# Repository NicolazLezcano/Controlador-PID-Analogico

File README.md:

# Controlador PID Analógico: Diseño, Simulación e Implementación

Este repositorio contiene el desarrollo integral de un controlador PID analógico, desde el modelado teórico y la simulación hasta el diseño de PCB y la validación en hardware real.
---

---

## 📋 Características Técnicas
* **Topología:** Controlador PID Analógico.
* **Software de Diseño:** KiCad (v9.0.7).
* **Simulación:** LTspice (v26.0.1).
* **Diseño de PCB:** Single-layer con plano de masa (GND).
* **Documentación:** Informe técnico completo incluido en la carpeta `/docs`.

---

## 📈 Simulación en LTspice
Antes del diseño físico, se validó la respuesta temporal del controlador utilizando **LTspice**. El objetivo fue ajustar las constantes para minimizar el *overshoot* y optimizar el tiempo de establecimiento ($t_s$).

$$u(t) = K_p e(t) + K_i \int_{0}^{t} e(\tau) d\tau + K_d \frac{de(t)}{dt}$$

| Controlador PID | Respuesta al Escalón |
| :---: | :---: |
|  |  |

> **Nota:** Los archivos de simulación (`.asc`) están disponibles en la carpeta `/simulation` para su replicación.

---

## 🎨 Diseño de Hardware (KiCad)
El diseño del PCB se optimizó para facilitar el prototipado rápido y garantizar la integridad de la señal frente a ruidos e interferencias.

### Esquemático (Hoja Raíz)
Se utilizó un diseño jerárquico para separar las etapas de adquisición, procesamiento de error y potencia.

| Sensor | PID |
| :---: | :---: |
|  |  |

| PPM | Potencia |
| :---: | :---: |
|  |  |

### Layout y Ruteado
* **Integridad de Señal:** Se implementó un plano de masa (**Copper Pour**) para reducir la impedancia de retorno.
* **Single-Layer:** El ruteado se realizó exclusivamente en la capa inferior (**Back Copper**) para simplificar la manufactura manual.

| Ruteado de Pistas (Sin relleno) | Diseño Final (Con Plano de Masa) |
| :---: | :---: |
|  |  |

| Modelo 3D (Vista Frontal) | Modelo 3D (Vista Posterior) |
| :---: | :---: |
|  |  |

---

## 🛠️ Implementación y Resultados Reales
El proyecto concluyó con la fabricación física y la integración con el sensor y la carga, comparando los resultados experimentales con los simulados.

### Montaje y Calidad de Soldadura
| Vista Frontal (Componentes) | Vista Posterior (Soldadura) |
| :---: | :---: |
|  |  |

### Integración del Sistema
Se validó el lazo cerrado conectando el controlador a la carga (planta térmica) y al sensor de temperatura LM35DZ, verificando la estabilidad del sistema ante perturbaciones.

---

## 📂 Estructura del Repositorio
* `/kicad`: Archivos fuente del proyecto (`.kicad_pro`, `.kicad_sch`, `.kicad_pcb`).
* `/simulation`: Archivos de LTspice y capturas de ondas.
* `/img`: Imágenes, renders y capturas utilizadas en este README.
* `/docs`: Informe técnico detallado y lista de materiales (BOM).
* `/manufacturing`: Documentación de manufactura dividida en capas (`gerbers/`) y perforaciones (`drill/`). Incluye un archivo .zip listo para servicios de prototipado rápido.

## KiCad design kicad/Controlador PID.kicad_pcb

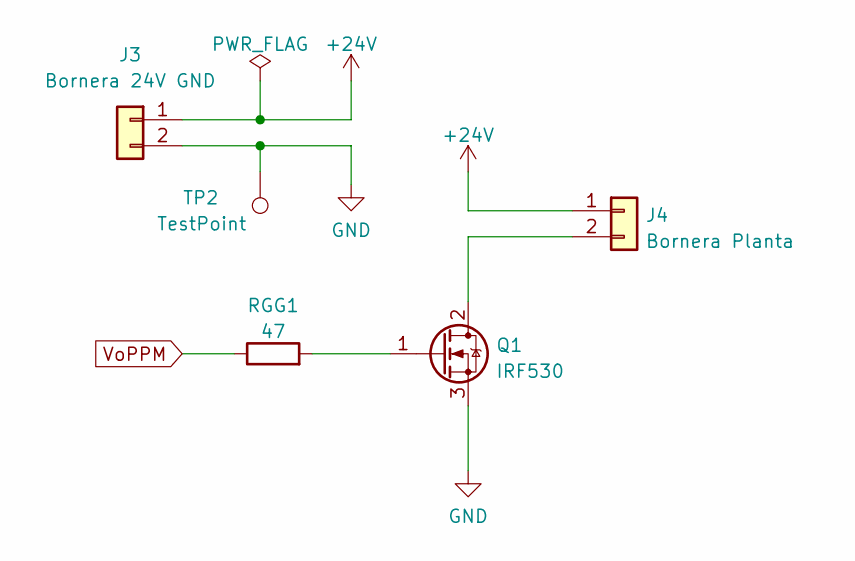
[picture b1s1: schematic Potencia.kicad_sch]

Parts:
J3: Bornera 24V GND; TerminalBlock_bornier-2_P5.08mm
J4: Bornera Planta; TerminalBlock_bornier-2_P5.08mm
Q1: IRF530; TO-220-3_Vertical Nico
RGG1: 47; R_Axial_DIN0207_L6.3mm_D2.5mm_P10.16mm_Horizontal Nico
TP2: TestPoint; PinHeader_1x01_P2.54mm_Vertical Nico

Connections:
+24V: J3.1, J4.1
GND: J3.2, Q1.3 (S), TP2.1; also elsewhere on the board
unnamed: J4.2, Q1.2 (D)
unnamed: Q1.1 (G), RGG1.2
VoPPM: RGG1.1; also elsewhere on the board

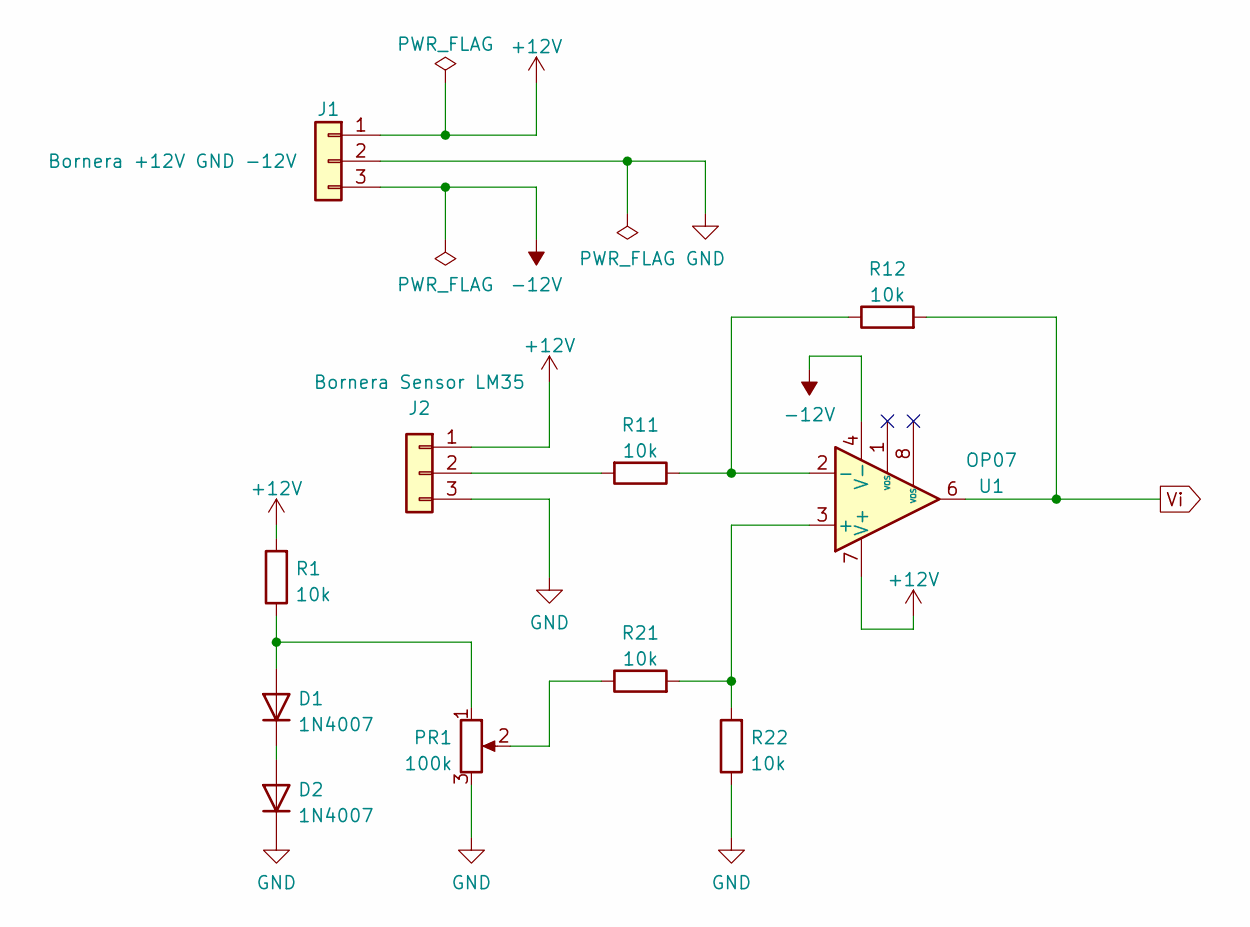
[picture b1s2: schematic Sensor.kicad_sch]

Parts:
D1, D2: 1N4007; D_DO-41_SOD81_P10.16mm_Horizontal
J1: Bornera +12V GND -12V; TerminalBlock_bornier-3_P5.08mm
J2: Bornera Sensor LM35; TerminalBlock_bornier-3_P5.08mm
PR1: 100k; Potentiometer_Piher_PC-16_Single_Horizontal
R1, R11, R12, R21, R22: 10k; R_Axial_DIN0207_L6.3mm_D2.5mm_P10.16mm_Horizontal Nico
U1: OP07; DIP-8_W7.62mm_LongPads Nico

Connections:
+12V: J1.1, J2.1, R1.2, U1.7 (V+); also elsewhere on the board
-12V: J1.3, U1.4 (V-); also elsewhere on the board
GND: D2.1 (K), J1.2, J2.3, PR1.3, R22.1; also elsewhere on the board
unnamed: D1.1 (K), D2.2 (A)
unnamed: D1.2 (A), PR1.1, R1.1
unnamed: J2.2, R11.2
unnamed: PR1.2, R21.1
unnamed: R11.1, R12.1, U1.2 (-)
unnamed: R21.2, R22.2, U1.3 (+)
Vi: R12.2, U1.6; also elsewhere on the board

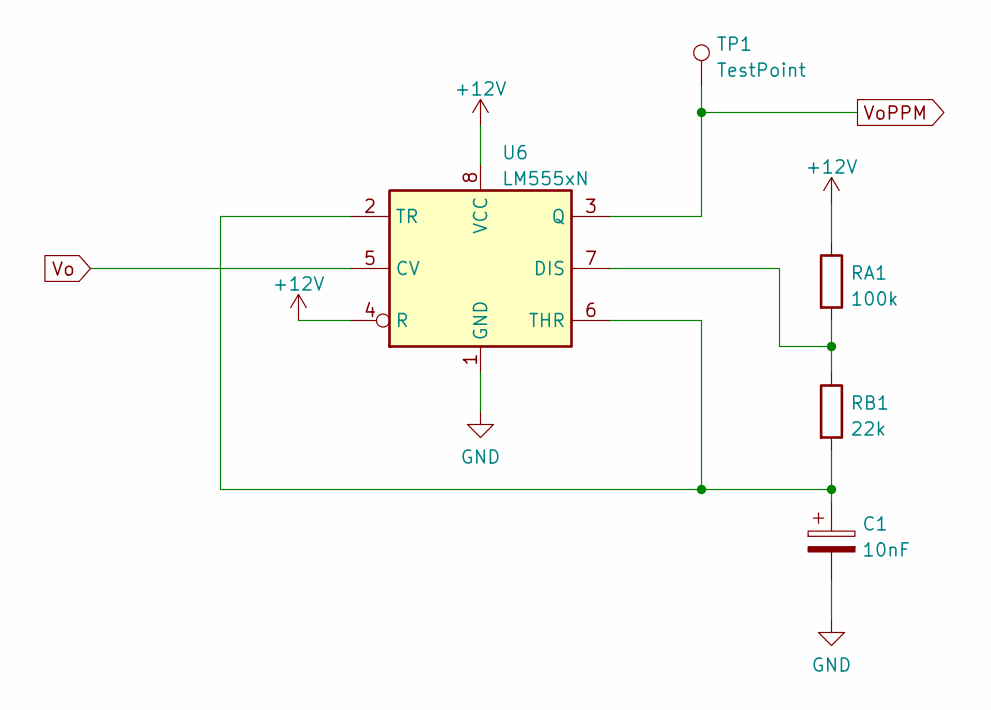
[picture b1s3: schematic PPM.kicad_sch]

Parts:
C1: 10nF; CP_Radial_D5.0mm_P2.50mm Nico
RA1: 100k; R_Axial_DIN0207_L6.3mm_D2.5mm_P10.16mm_Horizontal Nico
RB1: 22k; R_Axial_DIN0207_L6.3mm_D2.5mm_P10.16mm_Horizontal Nico
TP1: TestPoint; PinHeader_1x01_P2.54mm_Vertical Nico
U6: LM555xN; DIP-8_W7.62mm_LongPads Nico

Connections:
+12V: RA1.1, U6.4 (R), U6.8 (VCC); also elsewhere on the board
GND: C1.2, U6.1 (GND); also elsewhere on the board
unnamed: C1.1, RB1.2, U6.2 (TR), U6.6 (THR)
unnamed: RA1.2, RB1.1, U6.7 (DIS)
Vo: U6.5 (CV); also elsewhere on the board
VoPPM: TP1.1, U6.3 (Q); also elsewhere on the board

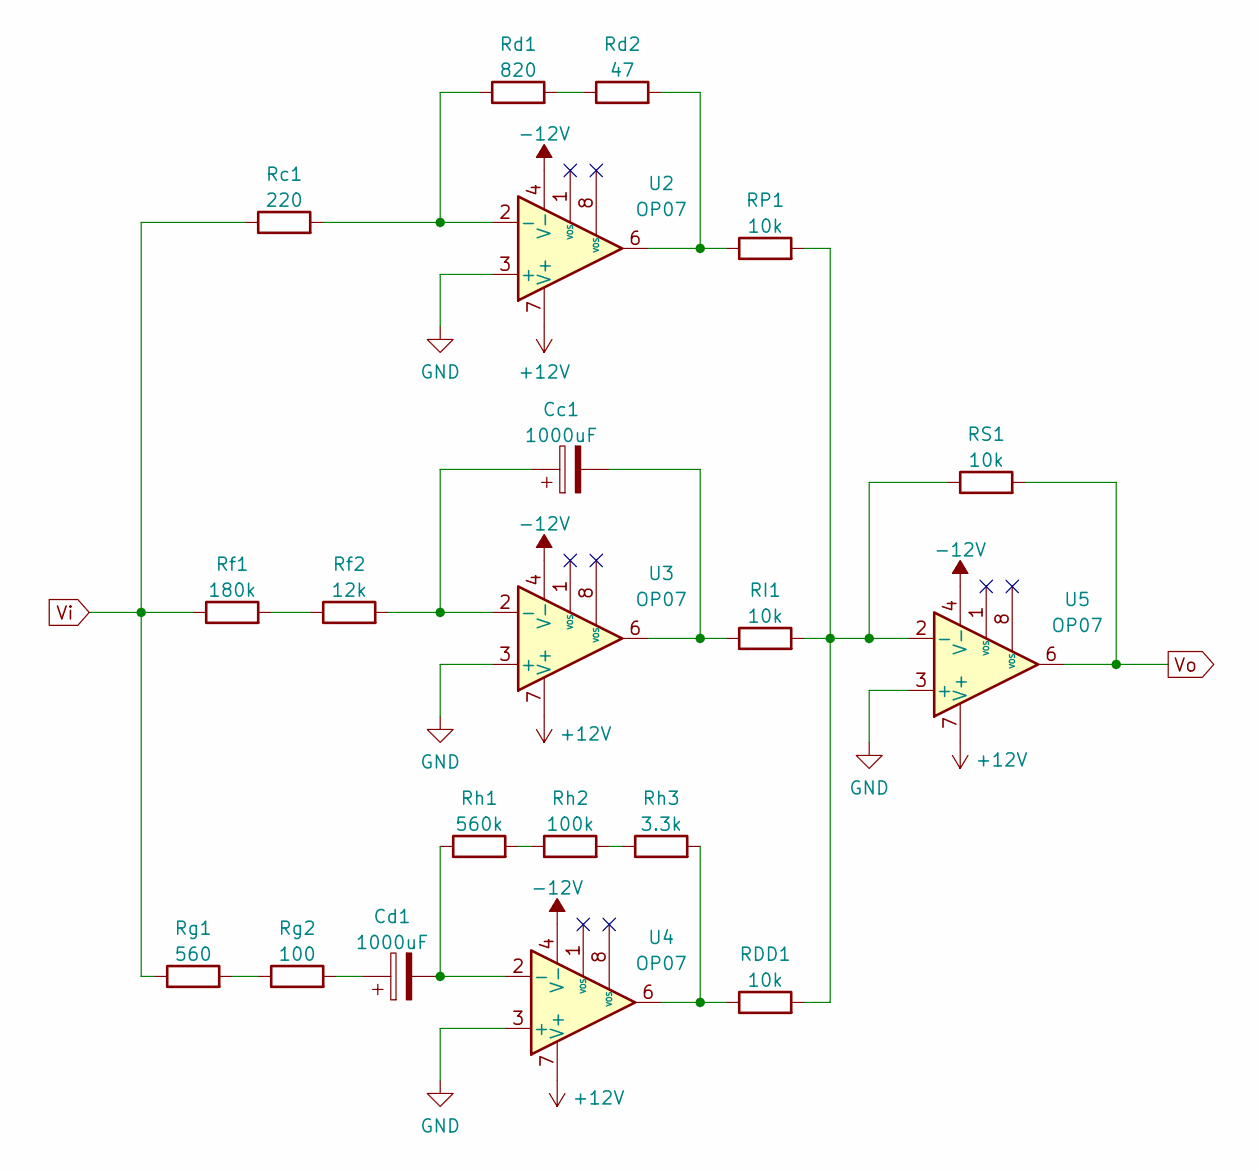
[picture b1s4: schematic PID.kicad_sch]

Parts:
Cc1: 1000uF; CP_Radial_D12.5mm_P5.00mm
Cd1: 1000uF; CP_Radial_D12.5mm_P5.00mm
RDD1: 10k; R_Axial_DIN0207_L6.3mm_D2.5mm_P10.16mm_Horizontal Nico
RI1: 10k; R_Axial_DIN0207_L6.3mm_D2.5mm_P10.16mm_Horizontal Nico
RP1: 10k; R_Axial_DIN0207_L6.3mm_D2.5mm_P10.16mm_Horizontal Nico
RS1: 10k; R_Axial_DIN0207_L6.3mm_D2.5mm_P10.16mm_Horizontal Nico
Rc1: 220; R_Axial_DIN0207_L6.3mm_D2.5mm_P10.16mm_Horizontal Nico
Rd1: 820; R_Axial_DIN0207_L6.3mm_D2.5mm_P10.16mm_Horizontal Nico
Rd2: 47; R_Axial_DIN0207_L6.3mm_D2.5mm_P10.16mm_Horizontal Nico
Rf1: 180k; R_Axial_DIN0207_L6.3mm_D2.5mm_P10.16mm_Horizontal Nico
Rf2: 12k; R_Axial_DIN0207_L6.3mm_D2.5mm_P10.16mm_Horizontal Nico
Rg1: 560; R_Axial_DIN0207_L6.3mm_D2.5mm_P10.16mm_Horizontal Nico
Rg2: 100; R_Axial_DIN0207_L6.3mm_D2.5mm_P10.16mm_Horizontal Nico
Rh1: 560k; R_Axial_DIN0207_L6.3mm_D2.5mm_P10.16mm_Horizontal Nico
Rh2: 100k; R_Axial_DIN0207_L6.3mm_D2.5mm_P10.16mm_Horizontal Nico
Rh3: 3.3k; R_Axial_DIN0207_L6.3mm_D2.5mm_P10.16mm_Horizontal Nico
U2, U3, U4, U5: OP07; DIP-8_W7.62mm_LongPads Nico

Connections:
+12V: U2.7 (V+), U3.7 (V+), U4.7 (V+), U5.7 (V+); also elsewhere on the board
-12V: U2.4 (V-), U3.4 (V-), U4.4 (V-), U5.4 (V-); also elsewhere on the board
GND: U2.3 (+), U3.3 (+), U4.3 (+), U5.3 (+); also elsewhere on the board
unnamed: Cc1.1, Rf2.2, U3.2 (-)
unnamed: Cc1.2, RI1.1, U3.6
unnamed: Cd1.1, Rg2.2
unnamed: Cd1.2, Rh1.1, U4.2 (-)
unnamed: RDD1.1, Rh3.2, U4.6
unnamed: RDD1.2, RI1.2, RP1.2, RS1.1, U5.2 (-)
unnamed: RP1.1, Rd2.2, U2.6
unnamed: Rc1.2, Rd1.1, U2.2 (-)
unnamed: Rd1.2, Rd2.1
unnamed: Rf1.2, Rf2.1
unnamed: Rg1.2, Rg2.1
unnamed: Rh1.2, Rh2.1
unnamed: Rh2.2, Rh3.1
Vi: Rc1.1, Rf1.1, Rg1.1; also elsewhere on the board
Vo: RS1.2, U5.6; also elsewhere on the board

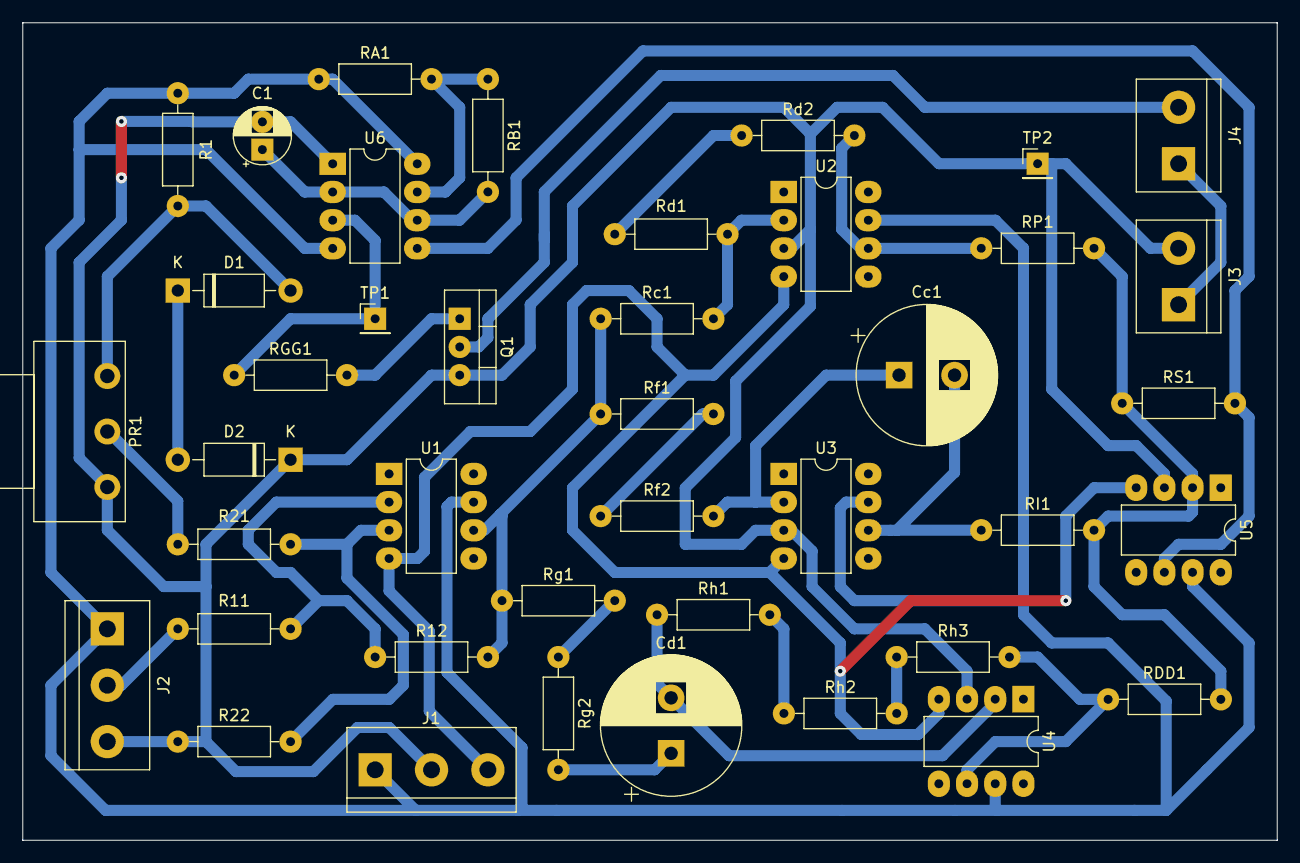
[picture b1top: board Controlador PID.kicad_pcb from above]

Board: 2 copper layers, 113.0 x 73.7 mm, 41 parts (0 on the bottom side), 30 nets.

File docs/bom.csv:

"Reference","Qty","Value","DNP","Exclude from BOM","Exclude from Board","Footprint","Datasheet"
"C1","1","10nF","","","","LibraryNico:CP_Radial_D5.0mm_P2.50mm Nico","~"
"Cc1,Cd1","2","1000uF","","","","Capacitor_THT:CP_Radial_D12.5mm_P5.00mm","~"
"D1,D2","2","1N4007","","","","Diode_THT:D_DO-41_SOD81_P10.16mm_Horizontal","~"
"J1","1","Bornera +12V GND -12V","","","","TerminalBlock:TerminalBlock_bornier-3_P5.08mm","~"
"J2","1","Bornera Sensor LM35","","","","TerminalBlock:TerminalBlock_bornier-3_P5.08mm","~"
"J3","1","Bornera 24V GND","","","","TerminalBlock:TerminalBlock_bornier-2_P5.08mm","~"
"J4","1","Bornera Planta","","","","TerminalBlock:TerminalBlock_bornier-2_P5.08mm","~"
"PR1","1","100k","","","","Potentiometer_THT:Potentiometer_Piher_PC-16_Single_Horizontal","~"
"Q1","1","IRF530","","","","LibraryNico:TO-220-3_Vertical Nico","http://www.irf.com/product-info/datasheets/data/irf540n.pdf"
"R1,R11,R12,R21,R22,RDD1,RI1,RP1,RS1","9","10k","","","","LibraryNico:R_Axial_DIN0207_L6.3mm_D2.5mm_P10.16mm_Horizontal Nico","~"
"RA1,Rh2","2","100k","","","","LibraryNico:R_Axial_DIN0207_L6.3mm_D2.5mm_P10.16mm_Horizontal Nico","~"
"RB1","1","22k","","","","LibraryNico:R_Axial_DIN0207_L6.3mm_D2.5mm_P10.16mm_Horizontal Nico","~"
"Rc1","1","220","","","","LibraryNico:R_Axial_DIN0207_L6.3mm_D2.5mm_P10.16mm_Horizontal Nico","~"
"Rd1","1","820","","","","LibraryNico:R_Axial_DIN0207_L6.3mm_D2.5mm_P10.16mm_Horizontal Nico","~"
"Rd2,RGG1","2","47","","","","LibraryNico:R_Axial_DIN0207_L6.3mm_D2.5mm_P10.16mm_Horizontal Nico","~"
"Rf1","1","180k","","","","LibraryNico:R_Axial_DIN0207_L6.3mm_D2.5mm_P10.16mm_Horizontal Nico","~"
"Rf2","1","12k","","","","LibraryNico:R_Axial_DIN0207_L6.3mm_D2.5mm_P10.16mm_Horizontal Nico","~"
"Rg1","1","560","","","","LibraryNico:R_Axial_DIN0207_L6.3mm_D2.5mm_P10.16mm_Horizontal Nico","~"
"Rg2","1","100","","","","LibraryNico:R_Axial_DIN0207_L6.3mm_D2.5mm_P10.16mm_Horizontal Nico","~"
"Rh1","1","560k","","","","LibraryNico:R_Axial_DIN0207_L6.3mm_D2.5mm_P10.16mm_Horizontal Nico","~"
"Rh3","1","3.3k","","","","LibraryNico:R_Axial_DIN0207_L6.3mm_D2.5mm_P10.16mm_Horizontal Nico","~"
"TP1,TP2","2","TestPoint","","","","LibraryNico:PinHeader_1x01_P2.54mm_Vertical Nico","~"
"U1,U2,U3,U4,U5","5","OP07","","","","LibraryNico:DIP-8_W7.62mm_LongPads Nico","https://www.analog.com/media/en/technical-documentation/data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"
"U6","1","LM555xN","","","","LibraryNico:DIP-8_W7.62mm_LongPads Nico","http://www.ti.com/lit/ds/symlink/lm555.pdf"

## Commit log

2026-02-02 Diseño completo y simulaciones del controlador PID
2026-02-02 Fix: remover carpeta de backups mal nombrada en gitignore
